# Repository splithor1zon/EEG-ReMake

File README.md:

# EEG-ReMake

*Accepting suggestions, just create a new issue.* 🤝

This project is based on work of OpenEEG project and Olimex's implementation of it. This project is free to use, but is bound by Creative Commons Attribution-Sharealike license. More info can be found at: <http://openeeg.sourceforge.net>

## Photos

For photos refer to [/img/README.md](/img/README.md)

## Schematics

The schematic and design files are in Autodesk Eagle file-formats. Inspired by: <https://www.olimex.com/Products/EEG/OpenEEG/EEG-SMT/>

## Documentation

I translated the original documentation and format shifted it to markdown. Documentation content list:

1. [Introduction](./doc/0_introduction.md)
1. [Theory](./doc/1_theory.md)
1. [Goals](./doc/2_goals.md)
1. [Methodology](./doc/3_methodology.md)
1. [Results](./doc/4_results.md)
1. [Discussion](./doc/5_discussion.md)
1. [Conclusion](./doc/6_conclusion.md)
1. [Literature](./doc/7_literature.md)

Please mind that this was a high school project and the documentation is not highly sophisticated. But I hope it will be of interest to you.

## The goal

The goal of this project was to customize EEG-SMT by Olimex and design electrodes producable in school environment. I tried to keep expandability of this system open by introducing few new connectors.

## Not perfect

This design definitely has its flaws, but it was tested and proved working. Using eye closing test while measuring at occipital lobe produced apparent alpha wave increase:

## Software

As for software, I used open-source project BrainBay, which can be found here: <http://www.shifz.org/brainbay/>

## Finished Product

I can also provide some guidelines on the final assembly.

## Interview about this project

<https://vedanadosah.cvtisr.sk/eeg-ako-studentsky-projekt>

Hopefully this project will help somebody. 🤗

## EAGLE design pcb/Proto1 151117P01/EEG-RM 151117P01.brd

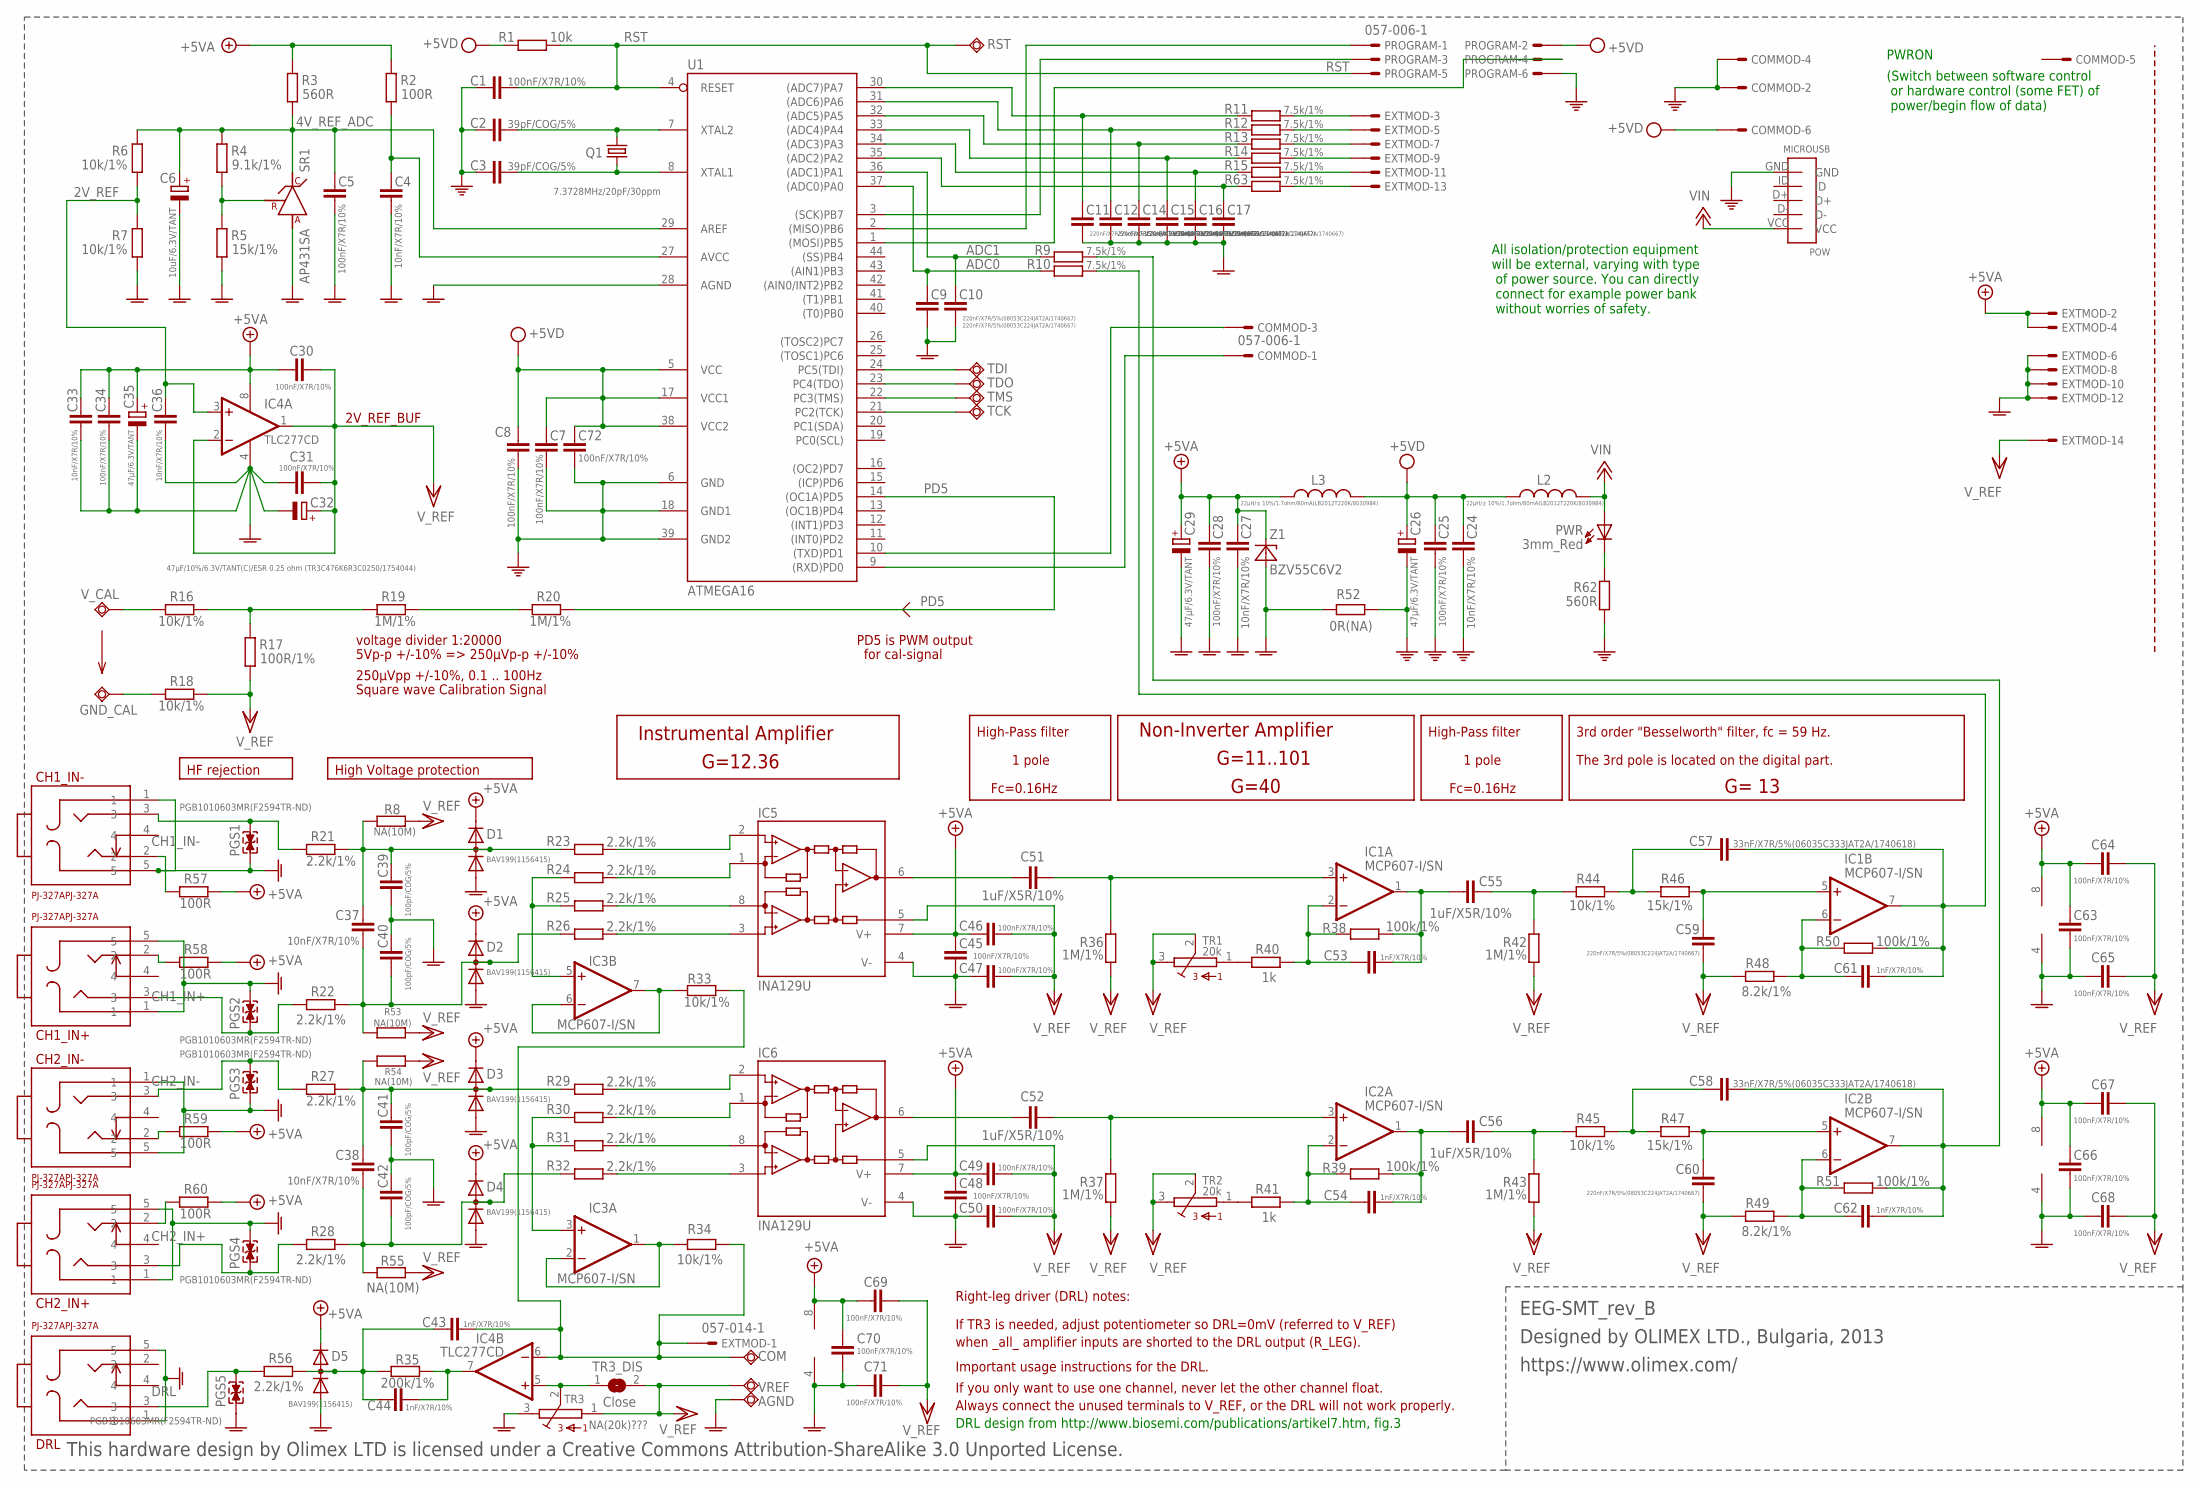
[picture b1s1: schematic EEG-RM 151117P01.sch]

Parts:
AGND: TESTPAD3; TEST_PAD40/70/SQUARE
C1, C5, C7, C8, C25, C28, C30, C31, C34, C45, C46, C47, C48, C49, C50, C63, C64, C65, C66, C67, C68, C69, C70, C71, C72: 100nF/X7R/10%; C2012
C2, C3: 39pF/COG/5%; C2012
C4, C24, C27, C33, C36, C37, C38: 10nF/X7R/10%; C2012
C6: 10uF/6.3V/TANT; CT3216
C9, C10, C11, C12, C14, C15, C16, C17, C59, C60: 220nF/X7R/5%(08053C224JAT2A/1740667); C2012
C26, C29, C35: 47µF/6.3V/TANT; CT3528
C32: 47µF/10%/6.3V/TANT(C)/ESR 0.25 ohm (TR3C476K6R3C0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; CT6032
C39, C40, C41, C42: 100pF/COG/5%; C2012
C43, C44, C53, C54, C61, C62: 1nF/X7R/10%; C2012
C51, C52, C55, C56: 1uF/X5R/10%; C2012
C57, C58: 33nF/X7R/5%(06035C333JAT2A/1740618); C2012
CH1_IN+, CH1_IN-, CH2_IN+, CH2_IN-: PJ-327APJ-327A; PJ-327A
COM: TESTPAD3; TEST_PAD40/70/SQUARE
COMMOD: 057-006-1
D1, D2, D3, D4, D5: BAV199(1156415); SOT23C(BAT54S)
DRL: PJ-327APJ-327A; PJ-327A
EXTMOD: 057-014-1
GND_CAL: TESTPAD3; TEST_PAD40/70/SQUARE
IC1, IC2, IC3: MCP607-I/SN; SO08
IC4: TLC277CD; SO08
IC5, IC6: INA129U; SO08
L2, L3: 22µH/± 10%/1.7ohm/80mA(LB2012T220K/8030984); L2012C
PGS1, PGS2, PGS3, PGS4, PGS5: PGB1010603MR(F2594TR-ND); 0603
POW: MICROUSB
PROGRAM: 057-006-1
PWR: 3mm_Red; LED-3.0MM
Q1: 7.3728MHz/20pF/30ppm; HC49/SMD2_THIN
R1: 10k; M2012
R2, R57, R58, R59, R60: 100R; M2012
R3, R62: 560R; M2012
R4: 9.1k/1%; M2012
R5, R46, R47: 15k/1%; M2012
R6, R7, R16, R18, R33, R34, R44, R45: 10k/1%; M2012
R8, R53, R54, R55: NA(10M); M2012
R9, R10, R11, R12, R13, R14, R15, R63: 7.5k/1%; M2012
R17: 100R/1%; M2012
R19, R20, R36, R37, R42, R43: 1M/1%; M2012
R21, R22, R23, R24, R25, R26, R27, R28, R29, R30, R31, R32, R56: 2.2k/1%; M2012
R35: 200k/1%; M2012
R38, R39, R50, R51: 100k/1%; M2012
R40, R41: 1k; M2012
R48, R49: 8.2k/1%; M2012
R52: 0R(NA); M2012
RST: TESTPAD80/30; SMD80/30
SR1: AP431SA; SOT-23
TCK: TESTPAD80/30; SMD80/30
TDI: TESTPAD80/30; SMD80/30
TDO: TESTPAD80/30; SMD80/30
TMS: TESTPAD80/30; SMD80/30
TR1, TR2: 20k; S64Y
TR3: NA(20k)???; S64Y
TR3_DIS: Close; SJ_1_SMALLER
U1: ATMEGA16; 44TQFP
VREF: TESTPAD3; TEST_PAD40/70/SQUARE
V_CAL: TESTPAD3; TEST_PAD40/70/SQUARE
Z1: BZV55C6V2; MINI-MELF

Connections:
2V_REF: C36.1, IC4.3 (+IN), R6.1, R7.2
4V_REF_ADC: C5.1, C6.+, R3.1, R4.2, R6.2, SR1.1 (C), U1.29 (AREF)
+5V: C27.1, C28.1, C29.+, C30.2, C33.1, C34.1, C35.+, C45.1, C46.1, C48.1, C49.1, C63.1, C64.1, C66.1, C67.1, C69.1, C70.1, D1.2 (K), D2.2 (K), D3.2 (K), D4.2 (K), D5.2 (K), EXTMOD.2, EXTMOD.4, IC1.8 (V+), IC2.8 (V+), IC3.8 (V+), IC4.8 (V+), IC5.7 (V+), IC6.7 (V+), L3.2, R2.2, R3.2, R57.2, R58.2, R59.2, R60.2, Z1.1 (C)
+12V: L2.1, POW.VCC, PWR.A
ADC0: C9.1, R10.1, U1.37 ((ADC0)PA0)
ADC1: C10.1, R9.1, U1.36 ((ADC1)PA1)
CH1_IN+: CH1_IN+.3, PGS2.1, R22.1
CH1_IN-: CH1_IN-.3, PGS1.2, R21.1
CH2_IN+: CH2_IN+.3, PGS4.1, R28.1
CH2_IN-: CH2_IN-.3, PGS3.2, R27.1
DRL: DRL.3, PGS5.2, R56.1
GNDA: AGND.P$1, C4.2, C5.2, C6.-, C9.2, C10.2, C11.2, C12.2, C14.2, C15.2, C16.2, C17.2, C27.2, C28.2, C29.-, C31.2, C32.-, C33.2, C34.2, C35.-, C36.2, C39.1, C40.2, C41.1, C42.2, C45.2, C47.1, C48.2, C50.1, C63.2, C65.1, C66.2, C68.1, C70.2, C71.1, CH1_IN+.1, CH1_IN+.5, CH1_IN-.1, CH1_IN-.5, CH2_IN+.1, CH2_IN+.5, CH2_IN-.1, CH2_IN-.5, D1.1 (A), D2.1 (A), D3.1 (A), D4.1 (A), D5.1 (A), DRL.1, DRL.5, EXTMOD.6, EXTMOD.8, EXTMOD.10, EXTMOD.12, IC1.4 (V-), IC2.4 (V-), IC3.4 (V-), IC4.4 (V-), IC5.4 (V-), IC6.4 (V-), PGS1.1, PGS2.2, PGS3.1, PGS4.2, PGS5.1, R5.1, R7.1, R52.1, SR1.3 (A), TR3.3, U1.28 (AGND), Z1.2 (A)
unnamed: CH1_IN-.2, R57.1
unnamed: CH1_IN+.2, R58.1
unnamed: TDI.P$1, U1.24 (PC5(TDI))
unnamed: TDO.P$1, U1.23 (PC4(TDO))
unnamed: TMS.P$1, U1.22 (PC3(TMS))
unnamed: TCK.P$1, U1.21 (PC2(TCK))
unnamed: CH2_IN-.2, R59.1
unnamed: C43.2, C44.2, D5.3 (AK), R35.1, R56.2
unnamed: CH2_IN+.2, R60.1
unnamed: PROGRAM.1, U1.2 ((MISO)PB6)
unnamed: PROGRAM.3, U1.3 ((SCK)PB7)
unnamed: PWR.K (C), R62.2
unnamed: PROGRAM.4, U1.1 ((MOSI)PB5)
unnamed: EXTMOD.3, R11.2
unnamed: C11.1, R11.1, U1.30 ((ADC7)PA7)
unnamed: C12.1, R12.1, U1.31 ((ADC6)PA6)
unnamed: EXTMOD.5, R12.2
unnamed: C4.1, R2.1, U1.27 (AVCC)
unnamed: R4.1, R5.2, SR1.2 (R)
unnamed: COMMOD.3, U1.10 ((TXD)PD1)
unnamed: COMMOD.1, U1.9 ((RXD)PD0)
unnamed: C17.1, R63.1, U1.35 ((ADC2)PA2)
unnamed: C16.1, R15.1, U1.34 ((ADC3)PA3)
unnamed: C3.1, Q1.2, U1.8 (XTAL1)
unnamed: C2.1, Q1.1, U1.7 (XTAL2)
unnamed: R40.2, TR1.1
unnamed: R41.2, TR2.1
unnamed: EXTMOD.11, R15.2
unnamed: EXTMOD.13, R63.2
unnamed: EXTMOD.7, R13.2
unnamed: EXTMOD.9, R14.2
unnamed: C14.1, R13.1, U1.32 ((ADC5)PA5)
unnamed: C15.1, R14.1, U1.33 ((ADC4)PA4)
unnamed: C55.2, R42.1, R44.1
unnamed: C51.1, IC5.6 (OUT)
unnamed: IC5.2 (-IN), R23.1
unnamed: IC5.1 (RG), R24.1
unnamed: C37.1, C40.1, D2.3 (AK), R22.2, R26.2, R53.2
unnamed: C37.2, C39.2, D1.3 (AK), R8.2, R21.2, R23.2
unnamed: C38.1, C42.1, D4.3 (AK), R28.2, R32.2, R55.2
unnamed: C38.2, C41.2, D3.3 (AK), R27.2, R29.2, R54.2
unnamed: IC5.8 (RG), R25.1
unnamed: C51.2, IC1.3 (+IN), R36.1
unnamed: IC3.5 (+IN), R24.2, R25.2
unnamed: C53.2, C55.1, IC1.1 (OUT), R38.2
unnamed: C53.1, IC1.2 (-IN), R38.1, R40.1
unnamed: IC5.3 (+IN), R26.1
unnamed: C59.1, IC1.5 (+IN), R46.2
unnamed: C57.1, R44.2, R46.1
unnamed: C57.2, C61.2, IC1.7 (OUT), R10.2, R50.2
unnamed: C61.1, IC1.6 (-IN), R48.1, R50.1
unnamed: C52.2, IC2.3 (+IN), R37.1
unnamed: C54.2, C56.1, IC2.1 (OUT), R39.2
unnamed: C54.1, IC2.2 (-IN), R39.1, R41.1
unnamed: C60.1, IC2.5 (+IN), R47.2
unnamed: C58.1, R45.2, R47.1
unnamed: C58.2, C62.2, IC2.7 (OUT), R9.2, R51.2
unnamed: C62.1, IC2.6 (-IN), R49.1, R51.1
unnamed: C56.2, R43.1, R45.1
unnamed: C52.1, IC6.6 (OUT)
unnamed: IC6.1 (RG), R30.1
unnamed: IC6.8 (RG), R31.1
unnamed: IC3.3 (+IN), R30.2, R31.2
unnamed: IC6.2 (-IN), R29.1
unnamed: IC6.3 (+IN), R32.1
unnamed: IC3.1 (OUT), IC3.2 (-IN), R34.2
unnamed: IC3.6 (-IN), IC3.7 (OUT), R33.2
unnamed: IC4.5 (+IN), TR3.2, TR3_DIS.1
unnamed: C44.1, IC4.7 (OUT), R35.2
unnamed: R19.2, R20.1
unnamed: C43.1, COM.P$1, EXTMOD.1, IC4.6 (-IN), R33.1, R34.1
unnamed: R16.2, R17.2, R19.1
unnamed: R16.1, V_CAL.P$1
unnamed: GND_CAL.P$1, R18.1
PD5: R20.2, U1.14 ((OC1A)PD5)
PE: C1.2, C2.2, C3.2, C7.2, C8.2, C24.2, C25.2, C26.-, C72.2, COMMOD.2, COMMOD.4, POW.GND, PROGRAM.6, R52.2, R62.1, U1.6 (GND), U1.18 (GND1), U1.39 (GND2)
RST: C1.1, PROGRAM.5, R1.2, RST.P$1, U1.4 (RESET)
VCC/2: C30.1, C31.1, C32.+, C46.2, C47.2, C49.2, C50.2, C59.2, C60.2, C64.2, C65.2, C67.2, C68.2, C69.2, C71.2, EXTMOD.14, IC4.1 (OUT), IC4.2 (-IN), IC5.5 (REF), IC6.5 (REF), R8.1, R17.1, R18.2, R36.2, R37.2, R42.2, R43.2, R48.2, R49.2, R53.1, R54.1, R55.1, TR1.2, TR1.3, TR2.2, TR2.3, TR3.1, TR3_DIS.2, VREF.P$1
VPP: C7.1, C8.1, C24.1, C25.1, C26.+, C72.1, COMMOD.6, L2.2, L3.1, PROGRAM.2, R1.1, U1.5 (VCC), U1.17 (VCC1), U1.38 (VCC2)

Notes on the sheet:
PD5 is PWM output
for cal-signal
250µVpp +/-10%, 0.1 .. 100Hz
Square wave Calibration Signal
voltage divider 1:20000
G=40
G=11..101
5Vp-p +/-10% => 250µVp-p +/-10%
3rd order "Besselworth" filter, fc = 59 Hz.
The 3rd pole is located on the digital part.
Fc=0.16Hz
HF rejection
High Voltage protection
High-Pass filter
Non-Inverter Amplifier
G= 13
1 pole
G=12.36
2V_REF_BUF
Instrumental Amplifier
DRL design from http://www.biosemi.com/publications/artikel7.htm, fig.3
If TR3 is needed, adjust potentiometer so DRL=0mV (referred to V_REF)
when _all_ amplifier inputs are shorted to the DRL output (R_LEG).
If you only want to use one channel, never let the other channel float.
Important usage instructions for the DRL.
Always connect the unused terminals to V_REF, or the DRL will not work properly.
Right-leg driver (DRL) notes:
This hardware design by Olimex LTD is licensed under a Creative Commons Attribution-ShareAlike 3.0 Unported License.
Designed by OLIMEX LTD., Bulgaria, 2013
https://www.olimex.com/
EEG-SMT_rev_B
PWRON
(Switch between software control or hardware control (some FET) of power/begin flow of data)
All isolation/protection equipment will be external, varying with type of power source. You can directly connect for example power bank without worries of safety.

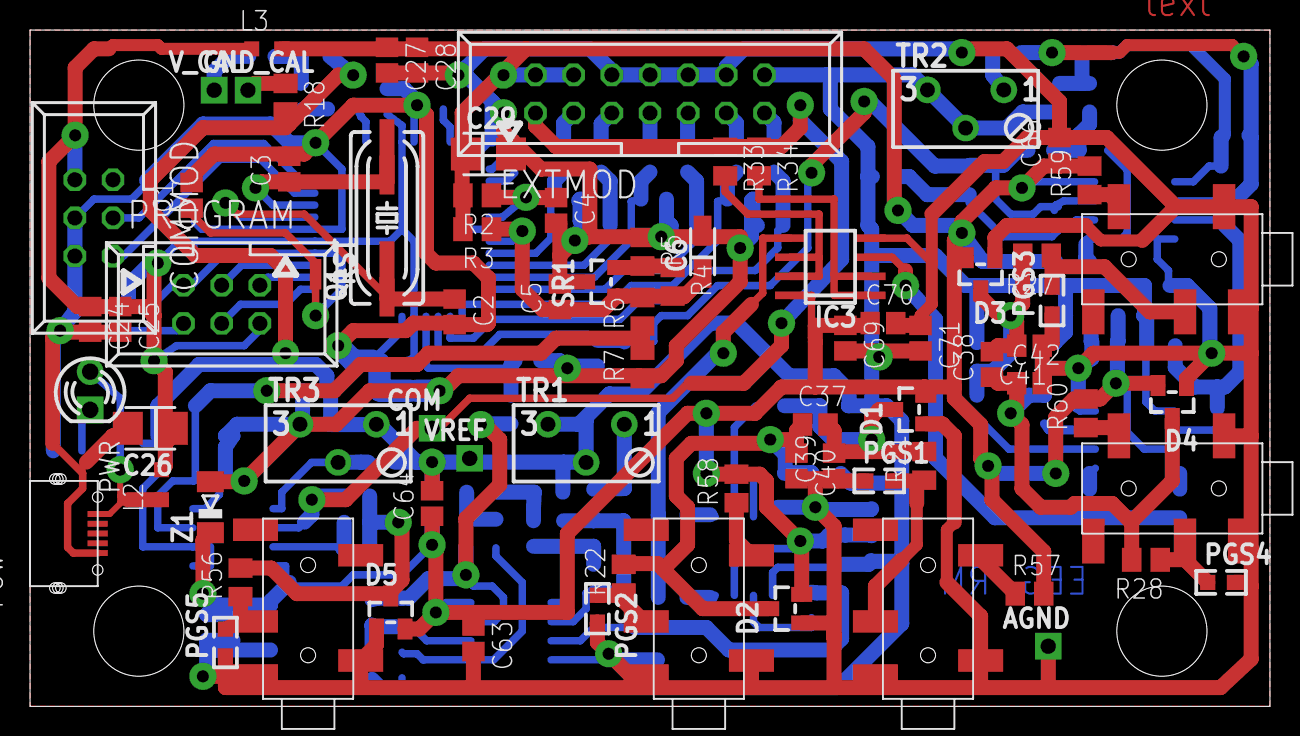
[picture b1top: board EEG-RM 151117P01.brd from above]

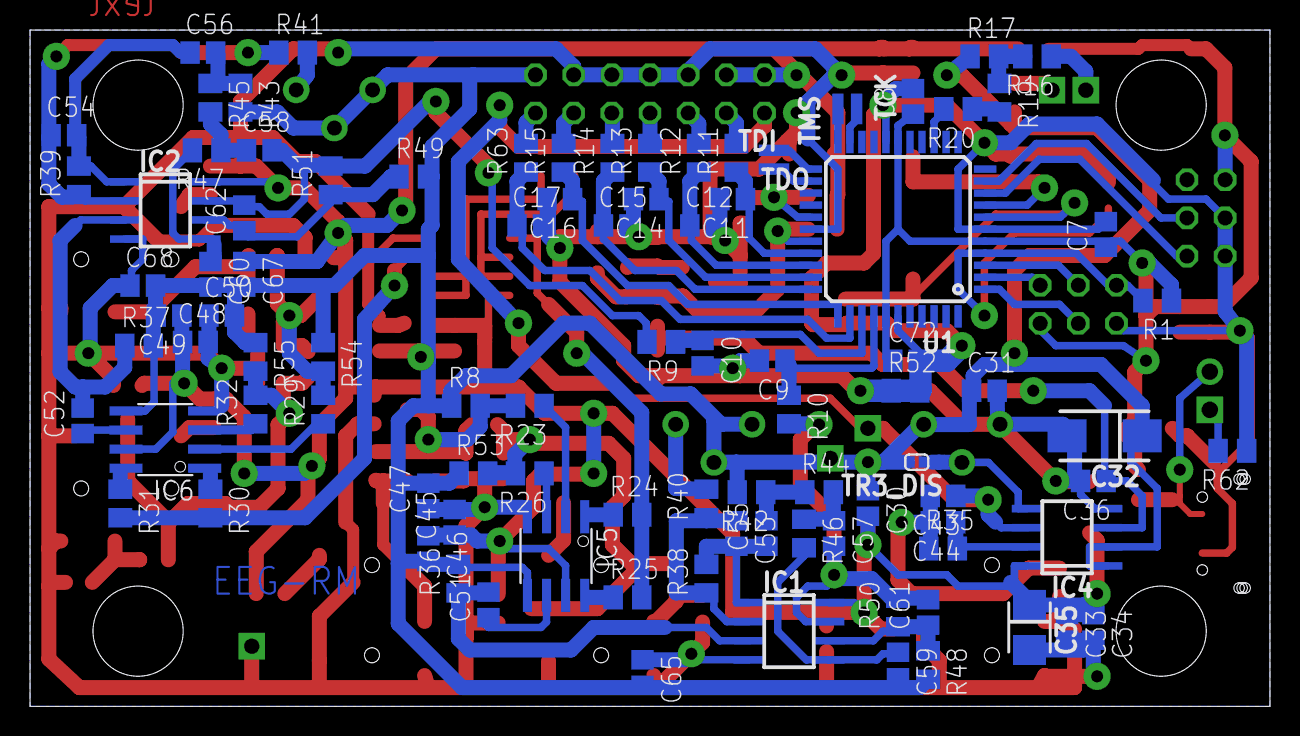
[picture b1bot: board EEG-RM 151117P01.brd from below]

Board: 2 copper layers, 82.5 x 45.0 mm, 173 parts (96 on the bottom side), 91 nets.

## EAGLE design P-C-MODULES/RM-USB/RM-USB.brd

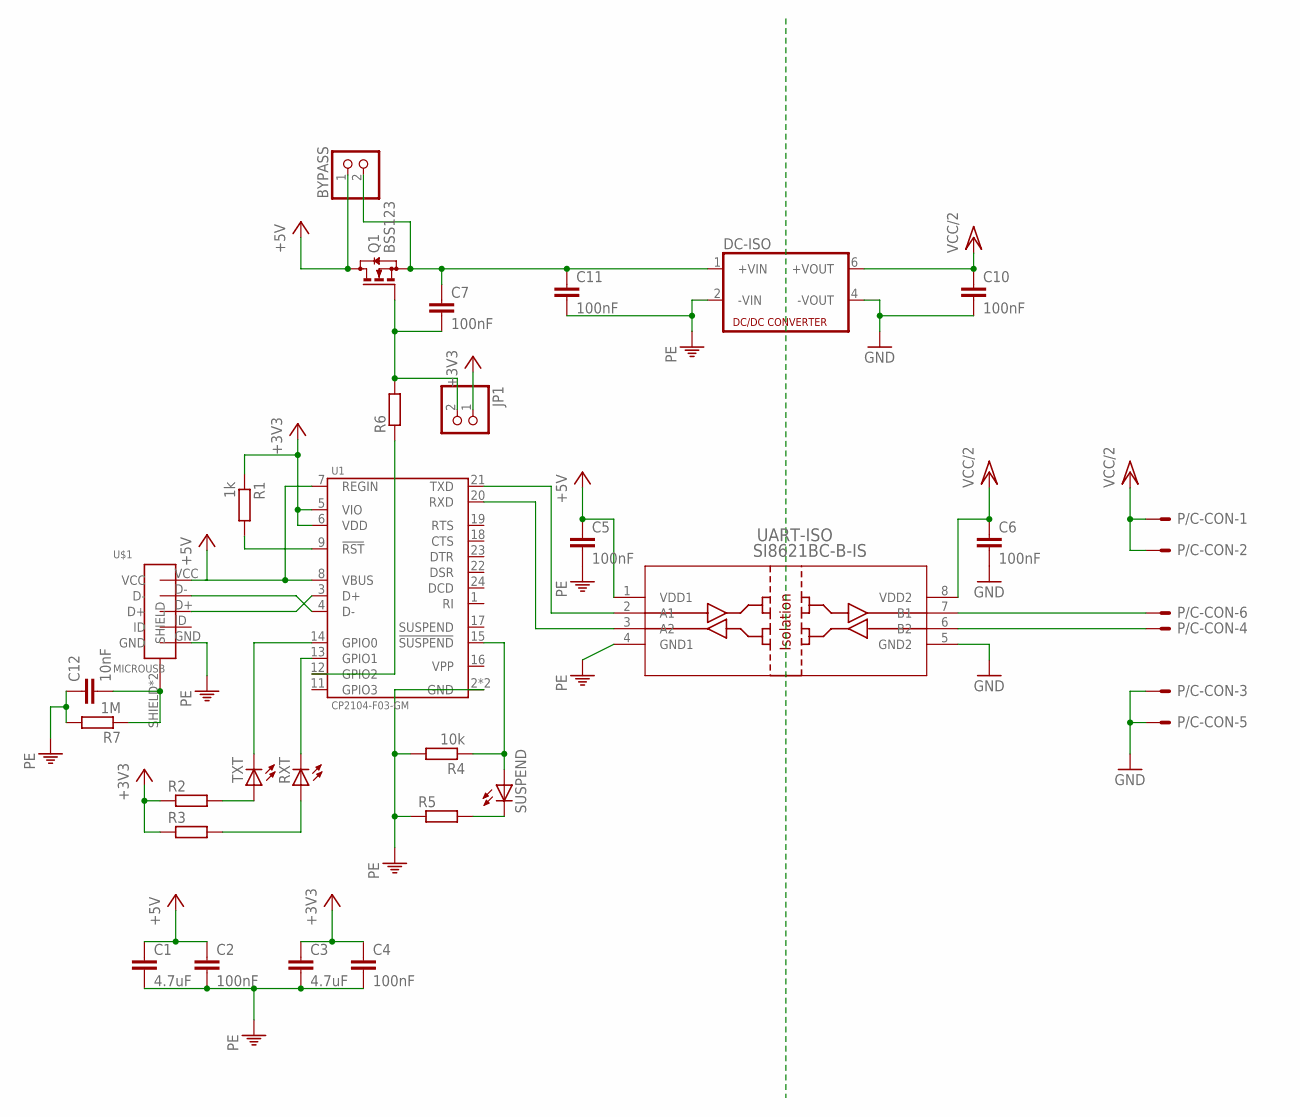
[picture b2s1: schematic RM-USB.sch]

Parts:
BYPASS: PINHD-1X2; 1X02
C1, C3: 4.7uF; C1206K
C2, C4, C5, C6, C7, C10, C11: 100nF; C0603
C12: 10nF; C0603
DC-ISO: NMA
JP1: PINHD-1X2; 1X02
P/C-CON: ML6EL; ML6L
Q1: BSS123; SOT23
R1: 1k; R0603
R2, R3, R5, R6: R-EU_R0603; R0603
R4: 10k; R0603
R7: 1M; R0603
RXT: LED3MM
SUSPEND: LED3MM
TXT: LED3MM
U1: CP2104-F03-GM; QFN-24-4X4
U$1: MICROUSB
UART-ISO: SI8621BC-B-IS; SOIC-8

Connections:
+3V3: C3.1, C4.1, JP1.1, R1.1, R2.1, R3.1, U1.5 (VIO), U1.6 (VDD)
+5V: BYPASS.1, C1.1, C2.1, C5.1, Q1.3 (D), U1.7 (REGIN), U1.8 (VBUS), U$1.VCC, UART-ISO.1 (VDD1)
GND: C6.2, C10.2, DC-ISO.4 (-VOUT), P/C-CON.3, P/C-CON.5, UART-ISO.5 (GND2)
unnamed: U1.4 (D-), U$1.D-
unnamed: U1.3 (D+), U$1.D+
unnamed: R1.2, U1.9 (!RST)
unnamed: R3.2, RXT.A
unnamed: TXT.K (C), U1.14 (GPIO0)
unnamed: RXT.K (C), U1.13 (GPIO1)
unnamed: R2.2, TXT.A
unnamed: U1.21 (TXD), UART-ISO.2 (A1)
unnamed: U1.20 (RXD), UART-ISO.3 (A2)
unnamed: P/C-CON.4, UART-ISO.6 (B2)
unnamed: P/C-CON.6, UART-ISO.7 (B1)
unnamed: R4.1, SUSPEND.A, U1.15 (!SUSPEND)
unnamed: BYPASS.2, C7.1, C11.1, DC-ISO.1 (+VIN), Q1.2 (S)
unnamed: R5.2, SUSPEND.K (C)
unnamed: C7.2, JP1.2, Q1.1 (G), R6.2
unnamed: C12.2, R7.1, U$1.SHIELD, U$1.SHIELD1 (SHIELD)
unnamed: R6.1, U1.12 (GPIO2)
PE: C1.2, C2.2, C3.2, C4.2, C5.2, C11.2, C12.1, DC-ISO.2 (-VIN), R4.2, R5.1, R7.2, U1.2 (GND), U1.PAD (GND), U$1.GND, UART-ISO.4 (GND1)
VCC/2: C6.1, C10.1, DC-ISO.6 (+VOUT), P/C-CON.1, P/C-CON.2, UART-ISO.8 (VDD2)

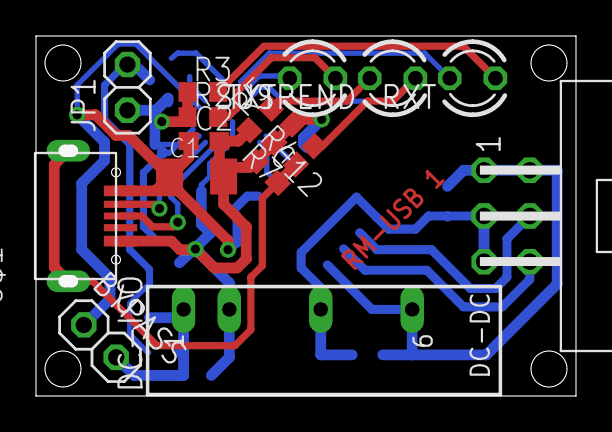
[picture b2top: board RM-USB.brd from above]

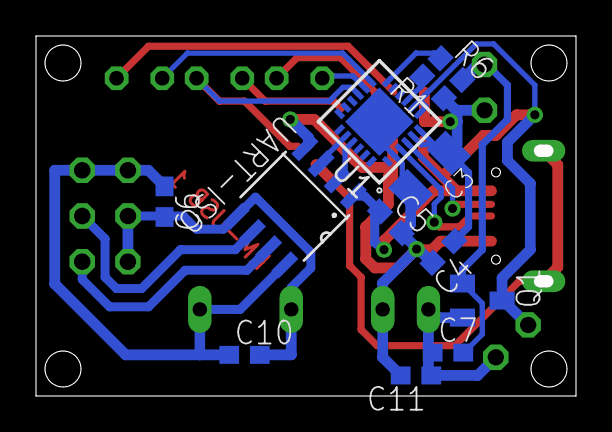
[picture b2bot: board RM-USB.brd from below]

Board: 2 copper layers, 29.3 x 19.3 mm, 28 parts (12 on the bottom side), 22 nets.

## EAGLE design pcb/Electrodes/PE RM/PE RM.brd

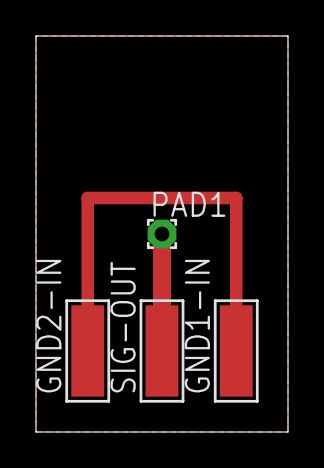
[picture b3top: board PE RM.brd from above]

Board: 2 copper layers, 14.0 x 22.0 mm, 4 parts (0 on the bottom side), 2 nets.

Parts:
GND1-IN, GND2-IN: WIREPADSMD5-1,8; 5-1,8
PAD1: WIREPAD1,6/0,8; 1,6/0,8
SIG-OUT: WIREPADSMD5-1,8; 5-1,8

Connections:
GND: GND1-IN.1, GND2-IN.1
SIG: PAD1.1, SIG-OUT.1

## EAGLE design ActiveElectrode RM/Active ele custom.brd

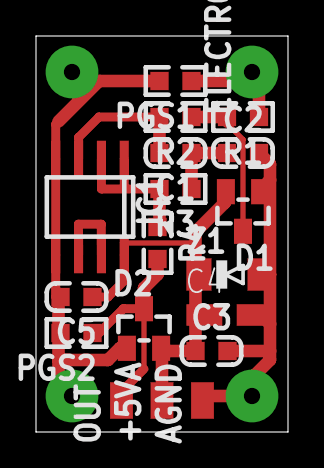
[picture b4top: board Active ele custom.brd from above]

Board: 2 copper layers, 14.0 x 22.0 mm, 19 parts (0 on the bottom side), 9 nets.

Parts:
+5VA: TESTPAD80/50; SMD80/50
AGND: TESTPAD80/50; SMD80/50
C1, C2: 100pF/COG/5%; C0603_DWS
C3: 100nF/X7R/10%; C0603_DWS
C4: 47µF/6.3V/TANT; CT3216
C5: 10nF/X7R/10%; C0603_DWS
D1, D2: BAV199(1156415); SOT23C(BAT54S)
ELECTRODE: TESTPAD80/50; SMD80/50
IC1: TL062CD; SO08
OUT: TESTPAD80/50; SMD80/50
PGS1, PGS2: PGB1010603MR(F2594TR-ND); 0603
R1, R2: 2.2k; R0603_5MIL_DWS
R3: 10k; R0603_5MIL_DWS
R4: 100R; R0603_5MIL_DWS
Z1: BZV55C6V2; MINI-MELF

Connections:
+5V: +5VA.P$1, C3.1, C4.+, C5.1, D1.2, D2.2, IC1.8, Z1.1
E-OUT: D2.3, OUT.P$1, PGS2.1, R4.2
ELECTRODE: ELECTRODE.P$1, PGS1.1, R1.1
GNDA: AGND.P$1, C2.2, C3.2, C4.-, C5.2, D1.1, D2.1, IC1.4, IC1.5, PGS1.2, PGS2.2, Z1.2
unnamed: IC1.6, IC1.7
unnamed: IC1.1, IC1.2, R3.2, R4.1
unnamed: C1.2, IC1.3, R2.2
unnamed: C1.1, C2.1, R3.1
unnamed: D1.3, R1.2, R2.1

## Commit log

2020-07-20 upload
2023-07-18 Rename img.md to README.md
2024-12-20 Big update, translated documentation to english, uploaded previous PCB designs
2024-12-21 Add component list to doc
